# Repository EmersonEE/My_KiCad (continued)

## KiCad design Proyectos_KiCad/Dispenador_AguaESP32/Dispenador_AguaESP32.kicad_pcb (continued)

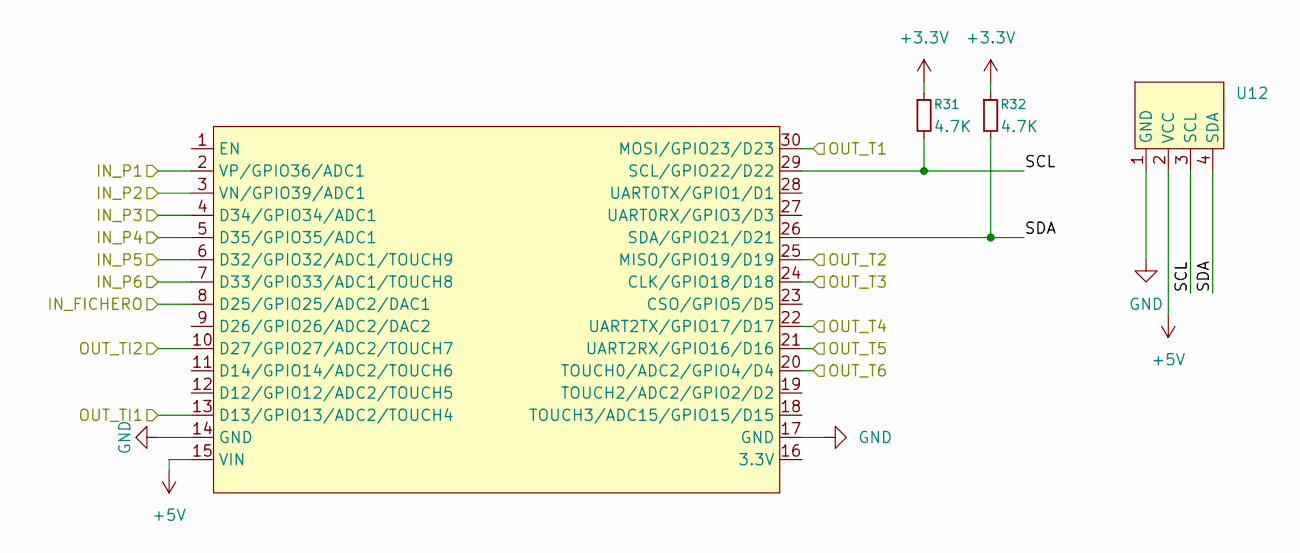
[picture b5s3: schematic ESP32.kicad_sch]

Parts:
R31, R32: 4.7K
U11: ESP32_DevKit_V1_DOIT; ESP32_DEVKIT_V1_E32
U12: Molex_KK-254_AE-6410-04A_1x04_P2.54mm_Vertical

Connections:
+3.3V: R31.1, R32.1; also elsewhere on the board
+5V: U11.15 (VIN), U12.2 (VCC); also elsewhere on the board
/ESP32/IN_FICHERO: U11.8 (D25/GPIO25/ADC2/DAC1); also elsewhere on the board
/ESP32/IN_P1: U11.2 (VP/GPIO36/ADC1); also elsewhere on the board
/ESP32/IN_P2: U11.3 (VN/GPIO39/ADC1); also elsewhere on the board
/ESP32/IN_P3: U11.4 (D34/GPIO34/ADC1); also elsewhere on the board
/ESP32/IN_P4: U11.5 (D35/GPIO35/ADC1); also elsewhere on the board
/ESP32/IN_P5: U11.6 (D32/GPIO32/ADC1/TOUCH9); also elsewhere on the board
/ESP32/IN_P6: U11.7 (D33/GPIO33/ADC1/TOUCH8); also elsewhere on the board
/ESP32/OUT_T1: U11.30 (MOSI/GPIO23/D23); also elsewhere on the board
/ESP32/OUT_T2: U11.25 (MISO/GPIO19/D19); also elsewhere on the board
/ESP32/OUT_T3: U11.24 (CLK/GPIO18/D18); also elsewhere on the board
/ESP32/OUT_T4: U11.22 (UART2TX/GPIO17/D17); also elsewhere on the board
/ESP32/OUT_T5: U11.21 (UART2RX/GPIO16/D16); also elsewhere on the board
/ESP32/OUT_T6: U11.20 (TOUCH0/ADC2/GPIO4/D4); also elsewhere on the board
/ESP32/OUT_TI1: U11.13 (D13/GPIO13/ADC2/TOUCH4); also elsewhere on the board
/ESP32/OUT_TI2: U11.10 (D27/GPIO27/ADC2/TOUCH7); also elsewhere on the board
/ESP32/SCL: R31.2, U11.29 (SCL/GPIO22/D22), U12.3 (SCL)
/ESP32/SDA: R32.2, U11.26 (SDA/GPIO21/D21), U12.4 (SDA)
GND: U11.14 (GND), U11.17 (GND), U12.1 (GND); also elsewhere on the board

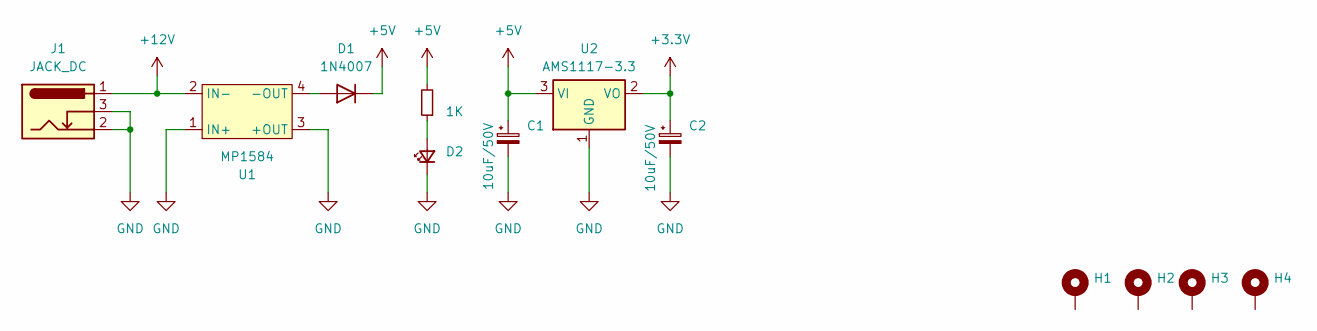
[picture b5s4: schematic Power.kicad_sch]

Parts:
C1, C2: 10uF/50V; CP_Radial_D4.0mm_P2.00mm
D1: 1N4007; D_DO-41_SOD81_P10.16mm_Horizontal
D2: LED_D5.0mm
H1, H2, H3, H4: MountingHole_3.2mm_M3_Pad_Via
J1: JACK_DC; BarrelJack_GCT_DCJ200-10-A_Horizontal
R1: 1K; 470
U1: MP1584; MP1584_Module
U2: AMS1117-3.3; SOT-223-3_TabPin2

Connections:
+3.3V: C2.1, U2.2 (VO); also elsewhere on the board
+5V: C1.1, D1.1 (K), R1.2, U2.3 (VI); also elsewhere on the board
+12V: J1.1, U1.2 (IN-); also elsewhere on the board
GND: C1.2, C2.2, D2.1 (K), J1.2, J1.3, U1.1 (IN+), U1.3 (+OUT), U2.1 (GND); also elsewhere on the board
unnamed: D1.2 (A), U1.4 (-OUT)
unnamed: D2.2 (A), R1.1

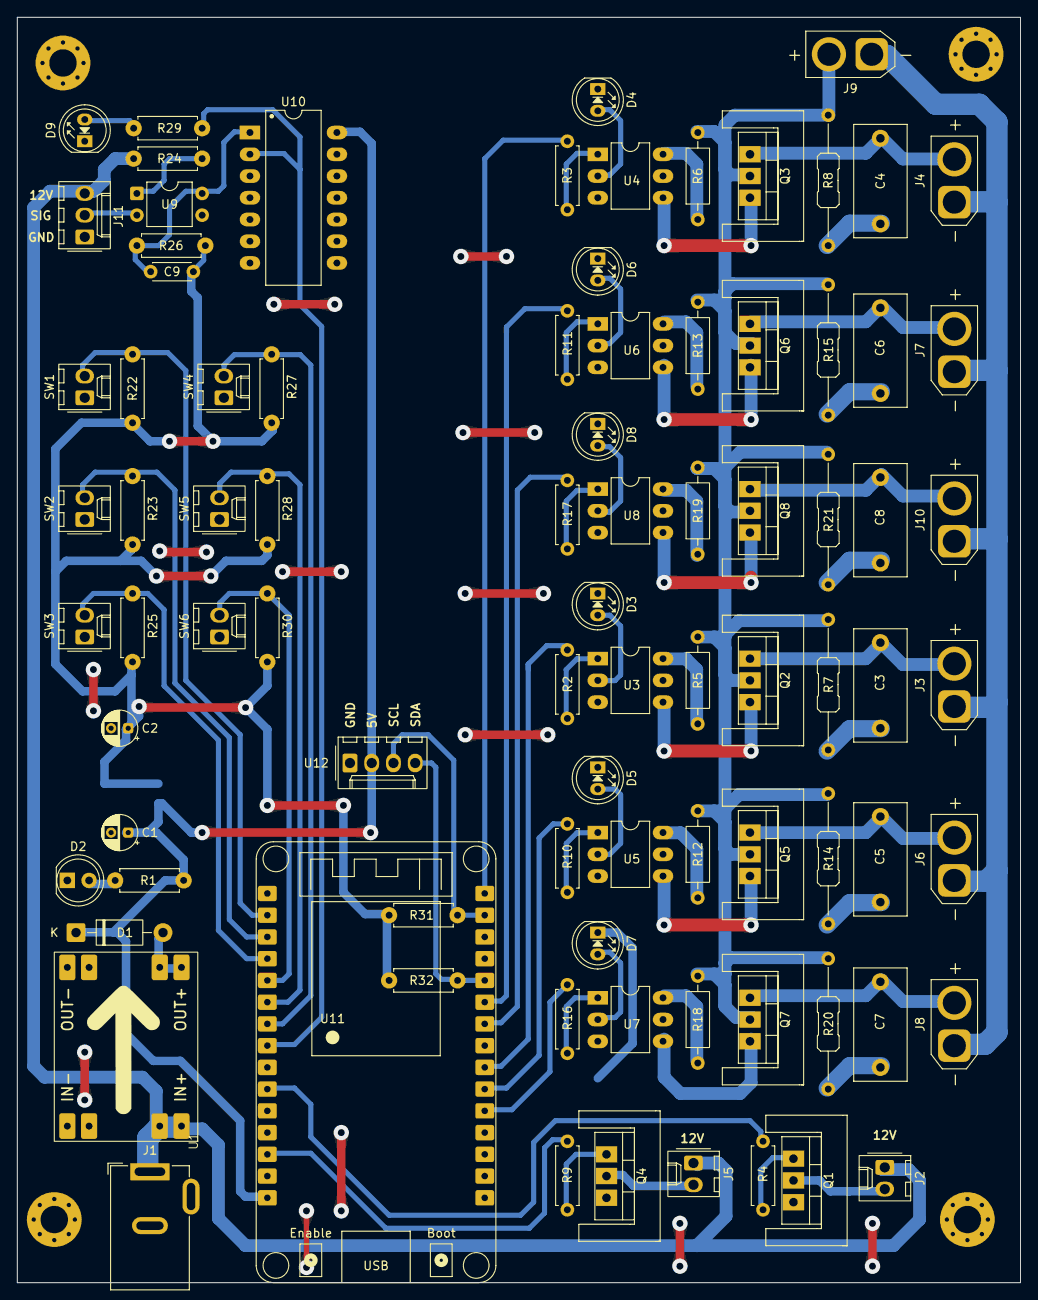
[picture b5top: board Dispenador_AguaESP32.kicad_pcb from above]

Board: 2 copper layers, 117.2 x 147.8 mm, 91 parts (1 on the bottom side), 69 nets.

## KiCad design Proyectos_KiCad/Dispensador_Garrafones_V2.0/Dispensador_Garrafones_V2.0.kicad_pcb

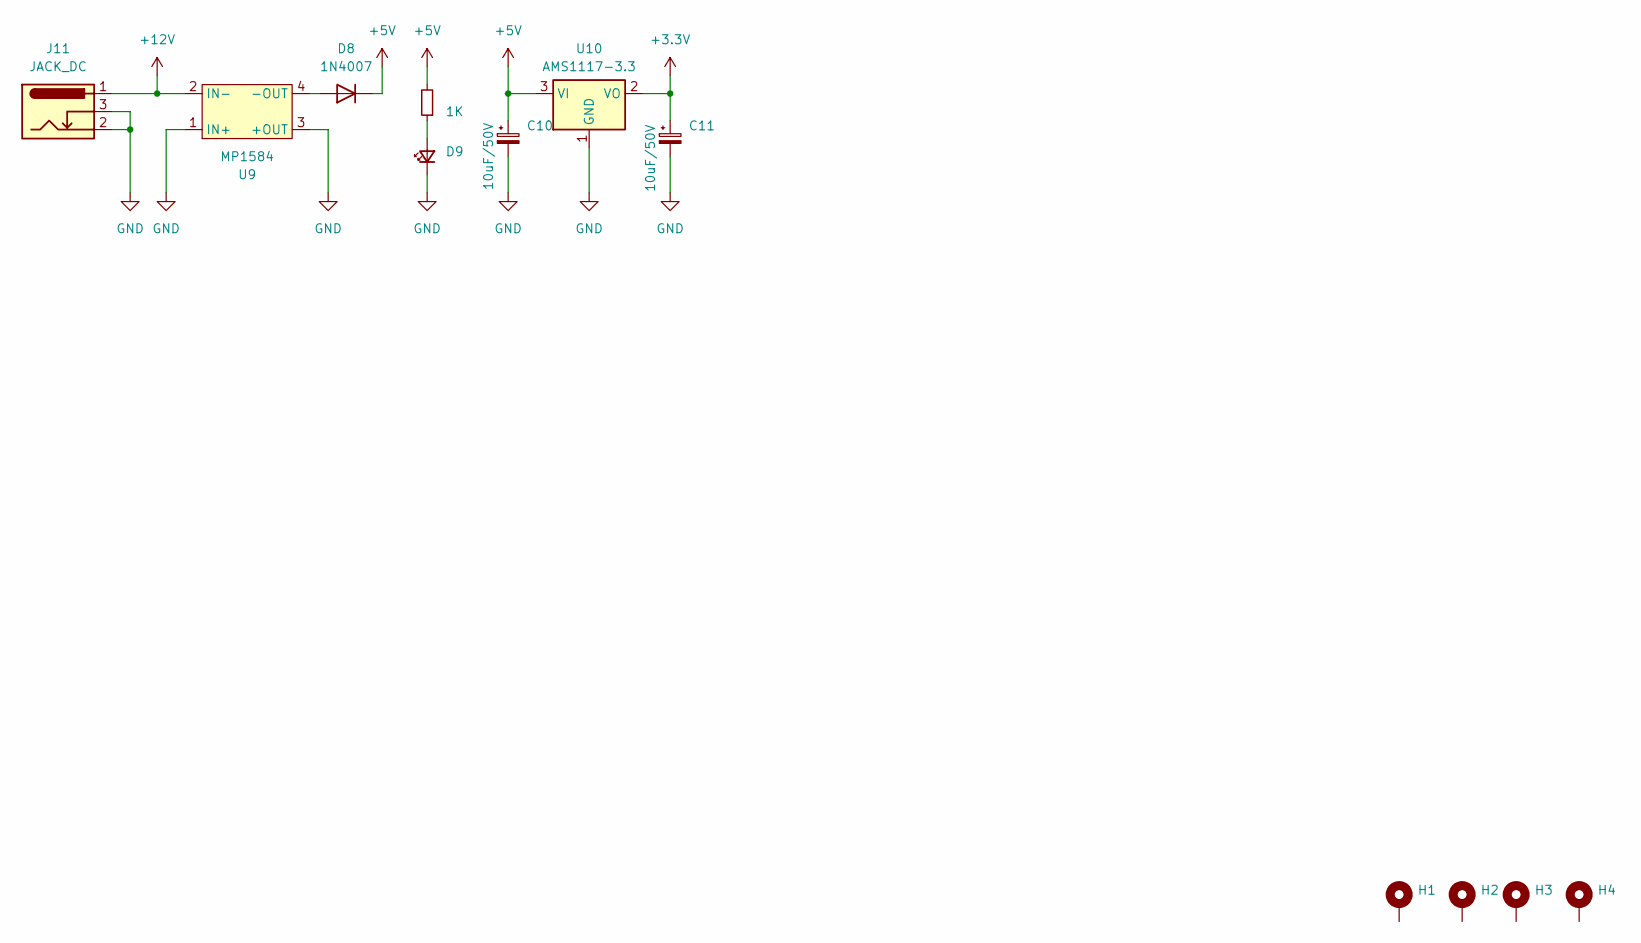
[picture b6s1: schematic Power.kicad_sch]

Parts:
C10, C11: 10uF/50V; CP_Radial_D4.0mm_P2.00mm
D8: 1N4007; D_DO-41_SOD81_P10.16mm_Horizontal
D9: LED_D5.0mm
H1, H2, H3, H4: MountingHole_3.2mm_M3_Pad_Via
J11: JACK_DC; BarrelJack_GCT_DCJ200-10-A_Horizontal
R30: 1K; 470
U9: MP1584; MP1584_Module
U10: AMS1117-3.3; SOT-223-3_TabPin2

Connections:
+3.3V: C11.1, U10.2 (VO); also elsewhere on the board
+5V: C10.1, D8.1 (K), R30.2, U10.3 (VI); also elsewhere on the board
+12V: J11.1, U9.2 (IN-); also elsewhere on the board
GND: C10.2, C11.2, D9.1 (K), J11.2, J11.3, U9.1 (IN+), U9.3 (+OUT), U10.1 (GND); also elsewhere on the board
unnamed: D8.2 (A), U9.4 (-OUT)
unnamed: D9.2 (A), R30.1

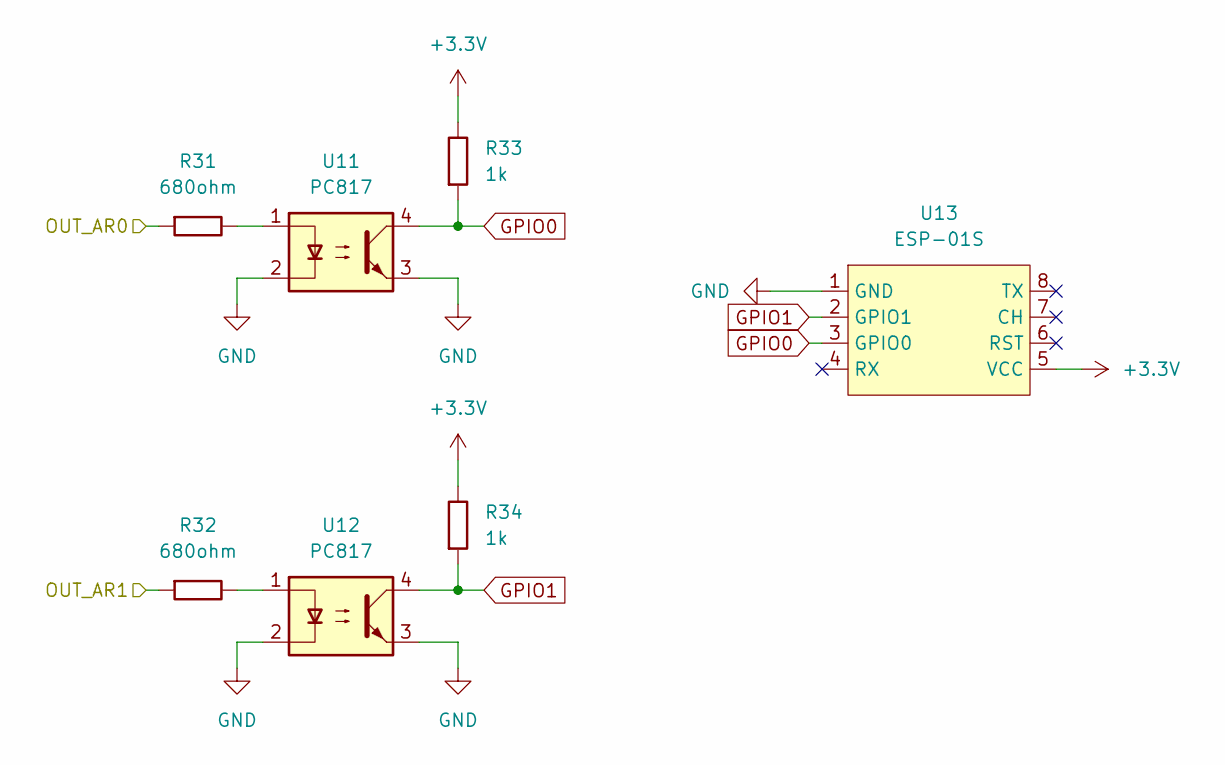
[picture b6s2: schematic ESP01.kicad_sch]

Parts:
R31, R32: 680ohm; 680
R33, R34: 1k; 1K
U11, U12: PC817; DIP-4_W7.62mm
U13: ESP-01S

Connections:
+3.3V: R33.2, R34.2, U13.5 (VCC); also elsewhere on the board
/ESP01/OUT_AR0: R31.1; also elsewhere on the board
/ESP01/OUT_AR1: R32.1; also elsewhere on the board
GND: U11.2, U11.3, U12.2, U12.3, U13.1 (GND); also elsewhere on the board
GPIO0: R33.1, U11.4, U13.3 (GPIO0)
GPIO1: R34.1, U12.4, U13.2 (GPIO1)
unnamed: R31.2, U11.1
unnamed: R32.2, U12.1

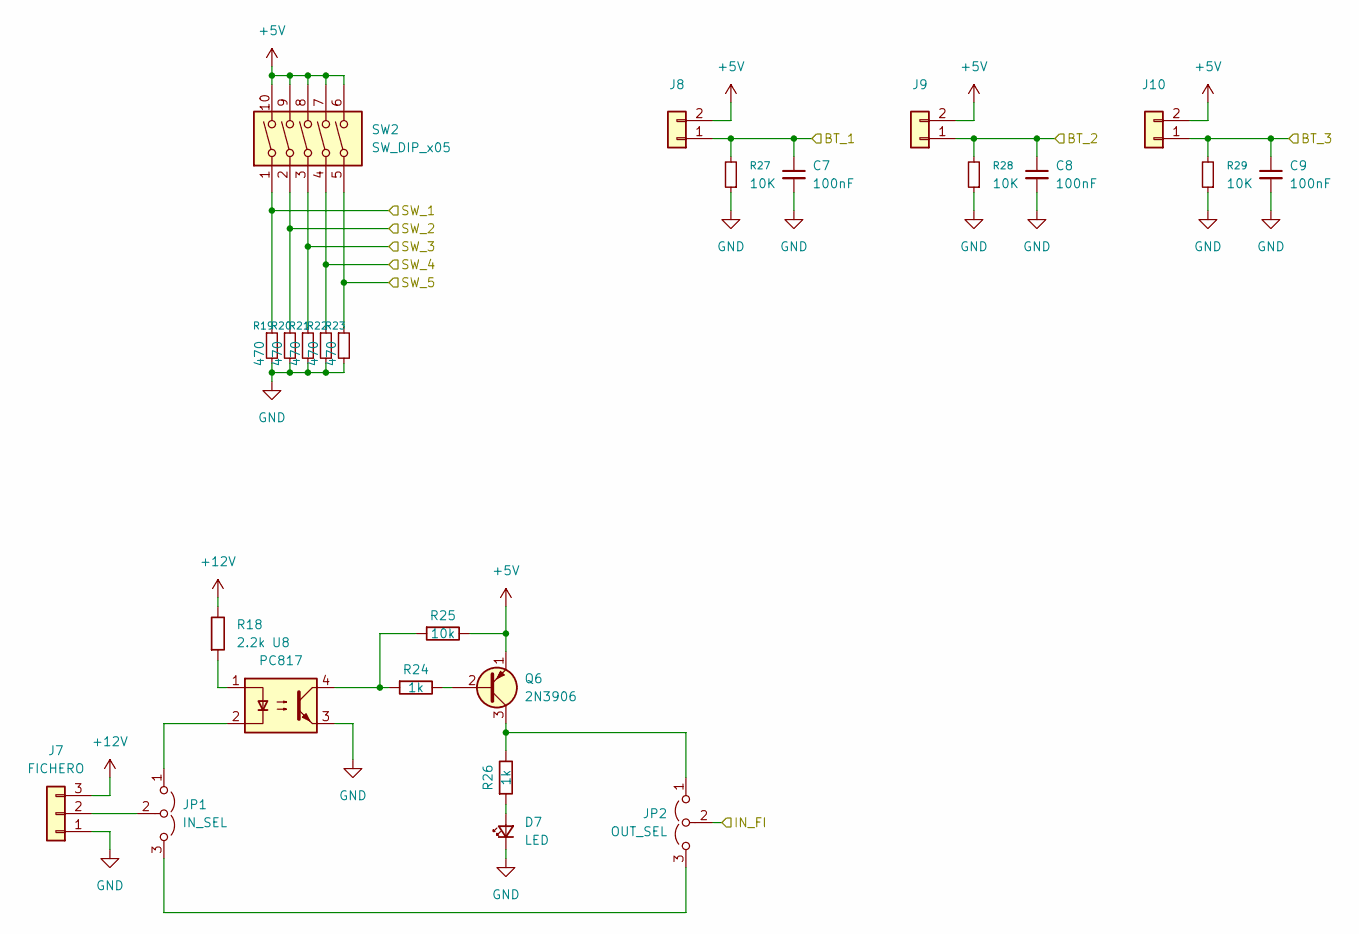
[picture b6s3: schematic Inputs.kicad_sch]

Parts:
C7, C8, C9: 100nF; C_Disc_D4.3mm_W1.9mm_P5.00mm
D7: LED; LED_G5.0mm
J7: FICHERO; Molex_KK-254_AE-6410-03A_1x03_P2.54mm_Vertical
J8, J9, J10: Molex_KK-254_AE-6410-02A_1x02_P2.54mm_Vertical
JP1: IN_SEL; PinHeader_1x03_P2.54mm_Vertical
JP2: OUT_SEL; PinHeader_1x03_P2.54mm_Vertical
Q6: 2N3906; TO-92_Inline_Wide_EBC
R18: 2.2k; 2.2K
R19, R20, R21, R22, R23: 470
R24, R26: 1k; 1K
R25: 10k; 10K
R27, R28, R29: 10K
SW2: SW_DIP_x05; SW_DIP_SPSTx05_Slide_9.78x14.88mm_W7.62mm_P2.54mm
U8: PC817; DIP-4_W7.62mm

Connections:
+5V: J8.2, J9.2, J10.2, Q6.1 (E), R25.2, SW2.6, SW2.7, SW2.8, SW2.9, SW2.10; also elsewhere on the board
+12V: J7.3, R18.2; also elsewhere on the board
/Inputs/BT_1: C7.1, J8.1, R27.2; also elsewhere on the board
/Inputs/BT_2: C8.1, J9.1, R28.2; also elsewhere on the board
/Inputs/BT_3: C9.1, J10.1, R29.2; also elsewhere on the board
/Inputs/IN_FI: JP2.2 (C); also elsewhere on the board
/Inputs/SW_1: R19.1, SW2.1; also elsewhere on the board
/Inputs/SW_2: R20.1, SW2.2; also elsewhere on the board
/Inputs/SW_3: R21.1, SW2.3; also elsewhere on the board
/Inputs/SW_4: R22.1, SW2.4; also elsewhere on the board
/Inputs/SW_5: R23.1, SW2.5; also elsewhere on the board
GND: C7.2, C8.2, C9.2, D7.1 (K), J7.1, R19.2, R20.2, R21.2, R22.2, R23.2, R27.1, R28.1, R29.1, U8.3; also elsewhere on the board
unnamed: D7.2 (A), R26.1
unnamed: J7.2, JP1.2 (C)
unnamed: JP1.1 (A), U8.2
unnamed: JP1.3 (B), JP2.3 (B)
unnamed: JP2.1 (A), Q6.3 (C), R26.2
unnamed: Q6.2 (B), R24.2
unnamed: R18.1, U8.1
unnamed: R24.1, R25.1, U8.4

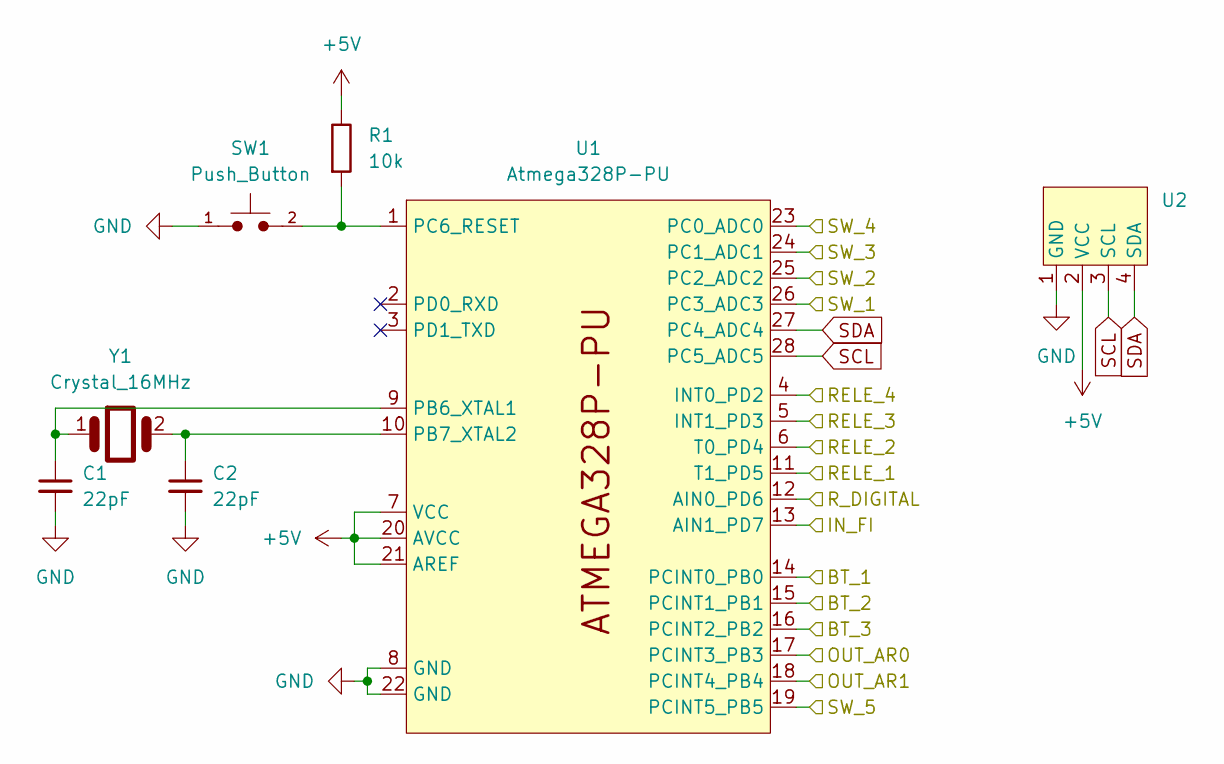
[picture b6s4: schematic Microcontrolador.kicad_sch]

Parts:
C1, C2: 22pF; C_Disc_D4.3mm_W1.9mm_P5.00mm
R1: 10k; 10K
SW1: Push_Button; SW_PUSH_6mm
U1: Atmega328P-PU; CERDIP-28_W7.62mm_SideBrazed_LongPads
U2: LCD ST7920
Y1: Crystal_16MHz; Crystal_HC49-4H_Vertical

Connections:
+5V: R1.2, U1.7 (VCC), U1.20 (AVCC), U1.21 (AREF), U2.2 (VCC); also elsewhere on the board
/ESP01/OUT_AR0: U1.17 (PCINT3_PB3); also elsewhere on the board
/ESP01/OUT_AR1: U1.18 (PCINT4_PB4); also elsewhere on the board
/Inputs/BT_1: U1.14 (PCINT0_PB0); also elsewhere on the board
/Inputs/BT_2: U1.15 (PCINT1_PB1); also elsewhere on the board
/Inputs/BT_3: U1.16 (PCINT2_PB2); also elsewhere on the board
/Inputs/IN_FI: U1.13 (AIN1_PD7); also elsewhere on the board
/Inputs/SW_1: U1.26 (PC3_ADC3); also elsewhere on the board
/Inputs/SW_2: U1.25 (PC2_ADC2); also elsewhere on the board
/Inputs/SW_3: U1.24 (PC1_ADC1); also elsewhere on the board
/Inputs/SW_4: U1.23 (PC0_ADC0); also elsewhere on the board
/Inputs/SW_5: U1.19 (PCINT5_PB5); also elsewhere on the board
/Microcontrolador/RELE_1: U1.11 (T1_PD5); also elsewhere on the board
/Microcontrolador/RELE_2: U1.6 (T0_PD4); also elsewhere on the board
/Microcontrolador/RELE_3: U1.5 (INT1_PD3); also elsewhere on the board
/Microcontrolador/RELE_4: U1.4 (INT0_PD2); also elsewhere on the board
/Microcontrolador/R_DIGITAL: U1.12 (AIN0_PD6); also elsewhere on the board
GND: C1.2, C2.2, SW1.1, U1.8 (GND), U1.22 (GND), U2.1 (GND); also elsewhere on the board
unnamed: C1.1, U1.9 (PB6_XTAL1), Y1.1
unnamed: C2.1, U1.10 (PB7_XTAL2), Y1.2
unnamed: R1.1, SW1.2, U1.1 (PC6_RESET)
SCL: U1.28 (PC5_ADC5), U2.3 (SCL)
SDA: U1.27 (PC4_ADC4), U2.4 (SDA)

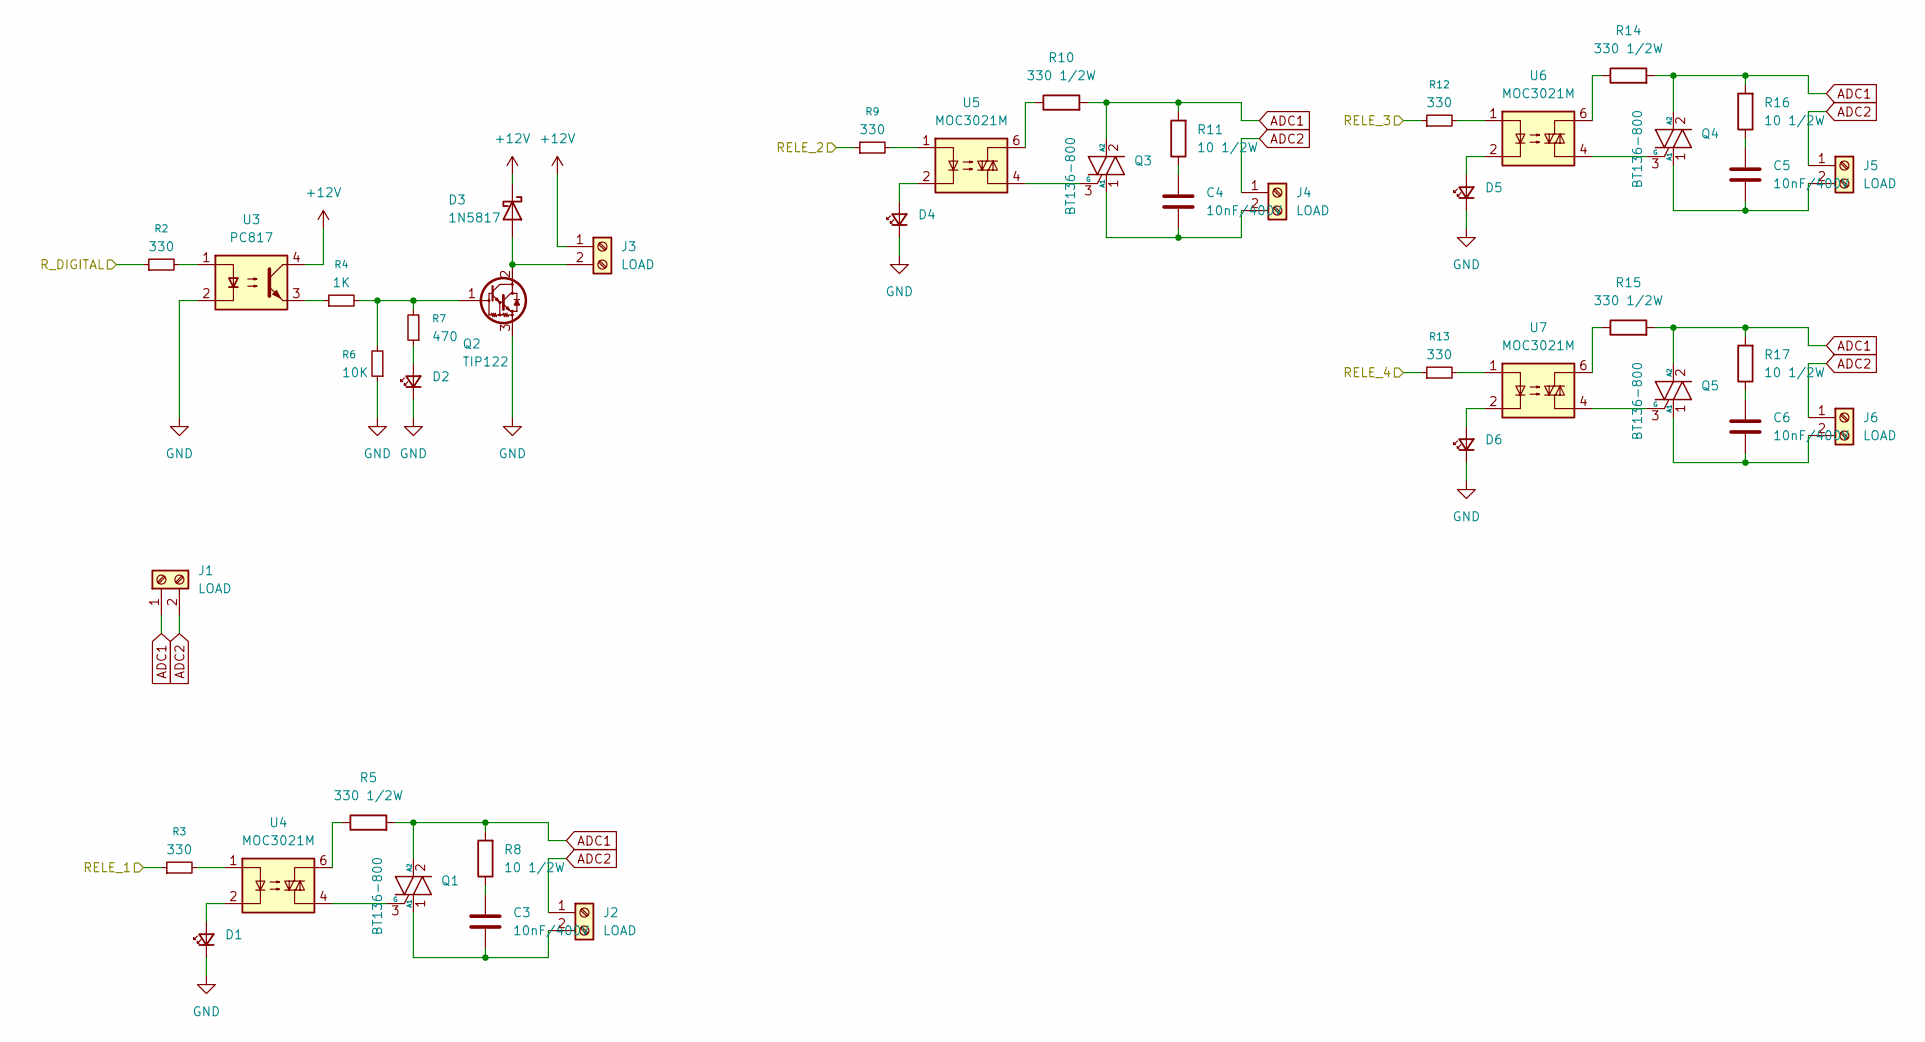
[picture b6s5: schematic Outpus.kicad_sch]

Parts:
C3, C4, C5, C6: 10nF/400V; C_Rect_L13.0mm_W6.0mm_P10.00mm_FKS3_FKP3_MKS4
D1, D2, D4, D5, D6: LED_D5.0mm
D3: 1N5817; D_DO-41_SOD81_P10.16mm_Horizontal
J1, J2, J4, J5, J6: LOAD; AMASS_XT30U-F_1x02_P5.0mm_Vertical
J3: LOAD; TerminalBlock_Phoenix_MKDS-1,5-2-5.08_1x02_P5.08mm_Horizont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
Q1, Q3, Q4, Q5: BT136-800; TO-3P-3_Vertical
Q2: TIP122; TO-220-3_VDC
R2, R3, R9, R12, R13: 330
R4: 1K
R5, R10, R14, R15: 330 1/2W; R_Axial_DIN0207_L6.3mm_D2.5mm_P10.16mm_Horizontal
R6: 10K
R7: 470
R8, R11, R16, R17: 10 1/2W; R_Axial_DIN0207_L6.3mm_D2.5mm_P15.24mm_Horizontal
U3: PC817; DIP-4_W7.62mm
U4, U5, U6, U7: MOC3021M; MOC3020

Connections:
+12V: D3.1 (K), J3.1, U3.4; also elsewhere on the board
/Microcontrolador/RELE_1: R3.1; also elsewhere on the board
/Microcontrolador/RELE_2: R9.1; also elsewhere on the board
/Microcontrolador/RELE_3: R12.1; also elsewhere on the board
/Microcontrolador/RELE_4: R13.1; also elsewhere on the board
/Microcontrolador/R_DIGITAL: R2.1; also elsewhere on the board
ADC1: J1.1, Q1.2 (A2), Q3.2 (A2), Q4.2 (A2), Q5.2 (A2), R5.2, R8.2, R10.2, R11.2, R14.2, R15.2, R16.2, R17.2
ADC2: J1.2, J2.1, J4.1, J5.1, J6.1
GND: D1.1 (K), D2.1 (K), D4.1 (K), D5.1 (K), D6.1 (K), Q2.3 (E), R6.1, U3.2; also elsewhere on the board
unnamed: C3.1, R8.1
unnamed: C4.1, R11.1
unnamed: C5.1, R16.1
unnamed: C6.1, R17.1
unnamed: D1.2 (A), U4.2
unnamed: D2.2 (A), R7.1
unnamed: D3.2 (A), J3.2, Q2.2 (C)
unnamed: D4.2 (A), U5.2
unnamed: D5.2 (A), U6.2
unnamed: D6.2 (A), U7.2
unnamed: C3.2, J2.2, Q1.1 (A1)
unnamed: C4.2, J4.2, Q3.1 (A1)
unnamed: C5.2, J5.2, Q4.1 (A1)
unnamed: C6.2, J6.2, Q5.1 (A1)
unnamed: Q1.3 (G), U4.4
unnamed: Q2.1 (B), R4.2, R6.2, R7.2
unnamed: Q3.3 (G), U5.4
unnamed: Q4.3 (G), U6.4
unnamed: Q5.3 (G), U7.4
unnamed: R2.2, U3.1
unnamed: R3.2, U4.1
unnamed: R4.1, U3.3
unnamed: R5.1, U4.6
unnamed: R9.2, U5.1
unnamed: R10.1, U5.6
unnamed: R12.2, U6.1
unnamed: R13.2, U7.1
unnamed: R14.1, U6.6
unnamed: R15.1, U7.6

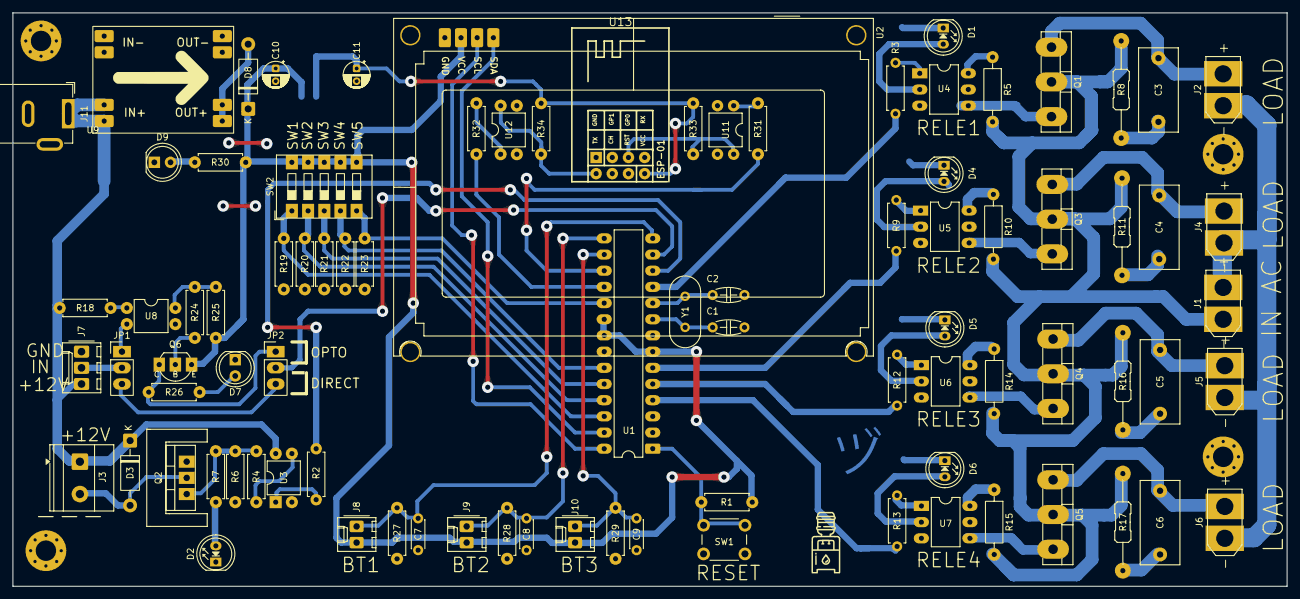
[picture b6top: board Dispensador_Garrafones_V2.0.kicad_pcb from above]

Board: 2 copper layers, 200.0 x 90.0 mm, 93 parts (1 on the bottom side), 70 nets.

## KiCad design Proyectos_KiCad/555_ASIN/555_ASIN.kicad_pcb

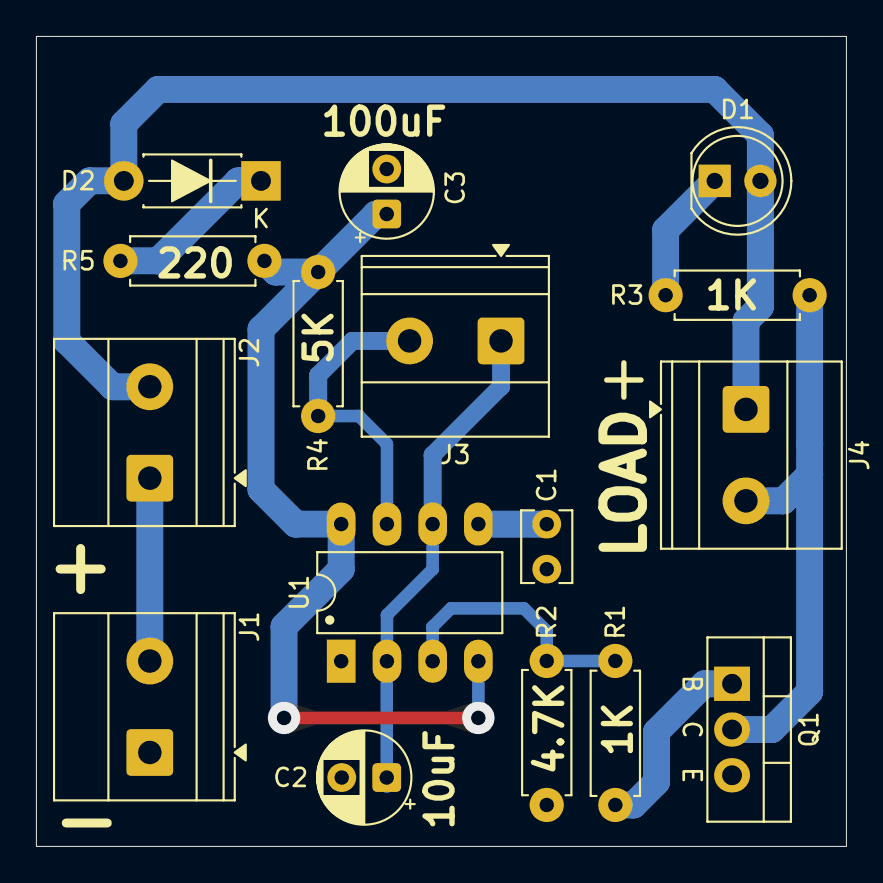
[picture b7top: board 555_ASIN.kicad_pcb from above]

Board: 2 copper layers, 45.0 x 45.0 mm, 16 parts (0 on the bottom side), 12 nets.

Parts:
C1: 10nF; C_Disc_D3.8mm_W2.6mm_P2.50mm
C2, C3: 10uF; CP_Radial_D5.0mm_P2.50mm
D1: LED_D5.0mm
D2: 1N4004; D_DO-41_SOD81_P7.62mm_Horizontal
J1: VINPUT; TerminalBlock_Phoenix_MKDS-1,5-2-5.08_1x02_P5.08mm_Horizont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
J2: SWITCH; TerminalBlock_Phoenix_MKDS-1,5-2-5.08_1x02_P5.08mm_Horizont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
J3: POT; TerminalBlock_Phoenix_MKDS-1,5-2-5.08_1x02_P5.08mm_Horizont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
J4: OUTPUT; TerminalBlock_Phoenix_MKDS-1,5-2-5.08_1x02_P5.08mm_Horizont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
Q1: TIP49; TO-220-3_Vertical_BCE
R1, R3: 1K
R2: 4.7K
R4: 5K; 5.1K
R5: 220
U1: 555; DIP-8_W7.62mm_LongPads

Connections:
GND: C1.2, C2.2, C3.2, J1.1, Q1.3 (E), R2.1, U1.1
unnamed: C1.1, U1.5
unnamed: D1.1 (K), R3.2
unnamed: D2.1 (K), R5.1
unnamed: J1.2, J2.1
unnamed: C2.1, J3.1, U1.2, U1.6
unnamed: J3.2, R4.1, U1.7
unnamed: J4.2, Q1.2 (C), R3.1
unnamed: Q1.1 (B), R1.2
unnamed: R1.1, R2.2, U1.3
VCC: D1.2 (A), D2.2 (A), J2.2, J4.1
VIN: C3.1, R4.2, R5.2, U1.4, U1.8

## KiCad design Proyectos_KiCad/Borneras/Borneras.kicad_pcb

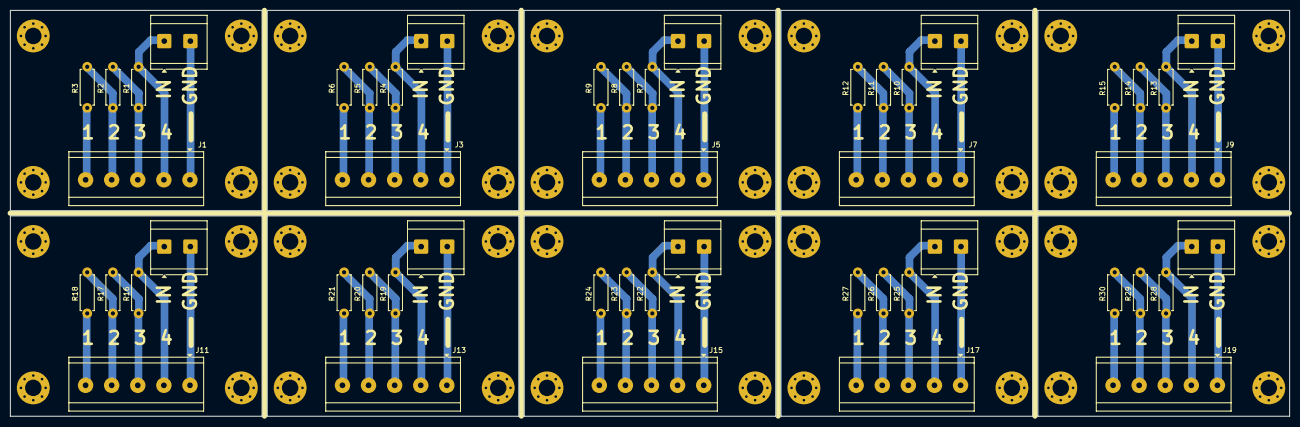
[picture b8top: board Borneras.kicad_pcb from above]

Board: 2 copper layers, 249.0 x 79.0 mm, 90 parts (0 on the bottom side), 5 nets.

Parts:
H1, H2, H3, H4, H5, H6, H7, H8, H9, H10, H11, H12, H13, H14, H15, H16, H17, H18, H19, H20, H21, H22, H23, H24, H25, H26, H27, H28, H29, H30, H31, H32, H33, H34, H35, H36, H37, H38, H39, H40: MountingHole_3.2mm_M3_Pad_Via
J1, J3, J5, J7, J9, J11, J13, J15, J17, J19: Screw_Terminal_01x05; TerminalBlock_CUI_TB007-508-05_1x05_P5.08mm_Horizontal
J2, J4, J6, J8, J10, J12, J14, J16, J18, J20: Screw_Terminal_01x02; TerminalBlock_CUI_TB007-508-02_1x02_P5.08mm_Horizontal
R1, R2, R3, R4, R5, R6, R7, R8, R9, R10, R11, R12, R13, R14, R15, R16, R17, R18, R19, R20, R21, R22, R23, R24, R25, R26, R27, R28, R29, R30: 100K

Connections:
unnamed: J1.1, J2.2, J3.1, J4.2, J5.1, J6.2, J7.1, J8.2, J9.1, J10.2, J11.1, J12.2, J13.1, J14.2, J15.1, J16.2, J17.1, J18.2, J19.1, J20.2
unnamed: J1.2, J2.1, J3.2, J4.1, J5.2, J6.1, J7.2, J8.1, J9.2, J10.1, J11.2, J12.1, J13.2, J14.1, J15.2, J16.1, J17.2, J18.1, J19.2, J20.1, R1.2, R4.2, R7.2, R10.2, R13.2, R16.2, R19.2, R22.2, R25.2, R28.2
unnamed: J1.3, J3.3, J5.3, J7.3, J9.3, J11.3, J13.3, J15.3, J17.3, J19.3, R1.1, R2.2, R4.1, R5.2, R7.1, R8.2, R10.1, R11.2, R13.1, R14.2, R16.1, R17.2, R19.1, R20.2, R22.1, R23.2, R25.1, R26.2, R28.1, R29.2
unnamed: J1.4, J3.4, J5.4, J7.4, J9.4, J11.4, J13.4, J15.4, J17.4, J19.4, R2.1, R3.2, R5.1, R6.2, R8.1, R9.2, R11.1, R12.2, R14.1, R15.2, R17.1, R18.2, R20.1, R21.2, R23.1, R24.2, R26.1, R27.2, R29.1, R30.2
unnamed: J1.5, J3.5, J5.5, J7.5, J9.5, J11.5, J13.5, J15.5, J17.5, J19.5, R3.1, R6.1, R9.1, R12.1, R15.1, R18.1, R21.1, R24.1, R27.1, R30.1

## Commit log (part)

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2025-04-19 Proyectos CachyOS
2025-05-17 Librerias
2025-05-29 NuevoSimbolo
2025-06-08 Por si cambio
2025-06-09 Agregando Resistencias
2025-06-14 Asistencia
2025-06-29 Agregando Disign Block
2025-06-29 Separando Proyectos
2025-06-30 Leds Colores
2025-07-05 Librerias y Esquematico
2025-07-06 Router
2025-07-06 Arreglando Leds
2025-07-14 Caja Terminada
2025-07-22 Todo por si cambio
2025-07-29 Placa entrenadora esp32-38
2025-08-04 Añadiendo Bloques SMD
2025-08-16 Articulaciones
2025-09-08 Punta Logica
2025-09-08 WS2812 NANO
2025-09-21 Por si cambio xd
2025-10-01 Agregando Modelos 3D
2025-10-01 AGregando Drivers
2025-10-01 Creando Huellas
2025-10-01 Placa Para el Brazo
2025-10-01 Placa Eddy
2025-10-03 Librerias Modificadas
2025-10-03 Placa Eddy Terminada
2025-10-03 Placa Brazo
2025-10-06 Añadiendo Lagrimas
2025-10-11 Por si cambio a gnome
2025-10-14 Agregando modulos INA219 - ACS712
2025-10-14 Routeo Termiando
2025-10-18 Cambiando a Omarchy
2025-10-21 Empezando Sumador-Restador
2025-11-15 Por si valgo
2025-11-28 Nuevos Esquematicos
2025-11-28 Placa 555 Astable
2025-11-28 555 PWM
2025-11-28 Placa Para sensor TPS
2025-11-28 Cambios Fuente
2025-11-30 Moviendo el RTC y el WEMOS
2025-12-08 Arreglando RAM
2026-01-24 Placa Entrenadora V2
2026-01-24 Bloques
2026-01-24 Hola
2026-03-03 Nuevos Proyectos
2026-03-20 Por si las dudas
2026-04-15 Shiel-ULN2803-BPM
2026-05-09 Omarchy-RIP
